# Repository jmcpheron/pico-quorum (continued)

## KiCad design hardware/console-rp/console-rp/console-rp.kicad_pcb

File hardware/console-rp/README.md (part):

# console-rp: the console on an RP2350, with no radio

*Design, 2026-10-29. Written by a script and read back by KiCad 10: the schematic (netlist and ERC)
and the board, routed (DRC). The fab files for JLCPCB are in [console-rp/fab/](console-rp/fab/) and
pass `tools/keypcb jlc console-rp`. Two real panels were checked against J2 ([The panel](#the-panel)).
Five ordered from JLCPCB on 2026-10-29, fully assembled
([the order](../../buildlog/2026-10-29-console-rp-order.md)), and received on 2026-11-04. Four of
them run the console's own image, and one is broken: [The boards and the
firmware](#the-boards-and-the-firmware) has each board and where its notes are.*

![console-rp from above: a warning triangle and EXPERIMENTAL HARDWARE COSIGNER over the 1.14-inch screen at the top left, PicoQuorum console-rp under it, and D0, D1 and D2 in a row below that; the flash, the RP2350, the crystal, the CH343P, and the key chip with an 8-bit key pointing at it, to its right; the USB-C on the right edge, RESET and BOOTSEL at the bottom right, and the bench header's holes along the top](renders/console-rp-top.jpg)

*KiCad's 3D render of the routed board. The panel is drawn as a box. More views are in
[renders/](renders/).*

[console-usb](../console-usb/README.md) took the radio out of use on an ESP32-S3. This board takes
it out of the chip: an **RP2350A** has none. The console talks to the world only through the USB-C
cable it is powered by. A program on the computer fetches the Safe's queue for it and posts its
signatures. The console still rebuilds every hash itself, and the key still signs only that.

```
   Safe's service ── HTTPS ── computer (the relay) ── USB-C ── CH343P ── UART1 ── RP2350A ── I2C0 ── ATECC608C
                              no key, no say in                              screen, D0 D1 D2
                              what gets signed
```

## Why an RP2350

The parts cost about the same as console-usb's: the RP2350A ($1.13 at 100) and its flash ($1.78)
against the S3's $2.52. What it buys is simpler:
- **No radio on the chip at all**, so nothing to keep switched off and no antenna rules.
- **The stock MicroPython image for the Pico 2** (not the W) runs on it, and the console already
  runs on an RP2350 (the Pico 2 W).
- **KiCad 10 ships the RP2350A's symbol and footprint**, and Raspberry Pi publishes the minimal
  circuit around it ("Hardware design with RP2350"). The circuit here is that one.

## Why a serial bridge, not the RP2350's own USB

The RP2350's own USB carries MicroPython's REPL. On this console the cable goes to a computer and
stays there, so any program on that computer could reach the REPL. From there it could make the chip
sign any digest, or call `machine.bootloader()` and write a new image. The bridge closes this with
wiring, as on console-usb:
- The USB-C's D+ and D− go to a **CH343P** (C2846043) and nothing else. It is a standard USB serial
  device (CDC-ACM), so no computer needs a driver.
- Its TXD and RXD go to **UART1** (GPIO21 and GPIO20). MicroPython never puts its REPL there.
- Its **DTR and RTS go nowhere.** The computer can't reset the RP2350 or hold BOOTSEL. DTR is also a
  strap at power-up, so it floats.
- The RP2350's own USB (through Raspberry Pi's 27 Ω) and SWD go to **J3**, a header that isn't
  fitted. Flashing needs J3 and a cable, or SWD and a debug probe: a person with the board in hand.

The generator checks this from KiCad's netlist and stops if it isn't so: the USB-C's data lines,
DTR and RTS, the RP2350's USB and SWD, RUN and BOOTSEL.

## The circuit

| block | parts | notes |
|---|---|---|
| the chip | U1 RP2350A (QFN-60), a 100n at each power pin | USB_OTP_VDD and QSPI_IOVDD share one, as the minimal design |
| its 1.1 V | L1 3.3 µH, C1 and C2 4.7 µF, R1 33 Ω and C3 4.7 µF on VREG_AVDD | the minimal design's. Raspberry Pi says to copy its layout and L1's orientation exactly |
| the clock | Y1 ABM8-272-T3 12 MHz, C15 and C16 15 pF, R2 1 kΩ into XOUT | the crystal and values Raspberry Pi asks for |
| the flash | U6 W25Q128JVSIQ, 16 MB, R3 1 kΩ and SW5 BOOTSEL on QSPI_SS | Basic at JLCPCB, so no fee. The Pico 2 image uses 4 MB of it |
| power | J1 USB-C (5.1k on CC1 and CC2), U2 USBLC6-2SC6, U3 XC6206P332MR | 200 mA is well over what the board draws |
| the link | U4 CH343P | VDD5 and VBUS from the USB-C, V3 on its own 100n, VIO at 3.3 V (WCH's datasheet, 5.2) |
| the key | U5 ATECC608C-SSHDA-T (SOIC-8), R6 and R7 4.7k on I2C0 | SOIC because JLCPCB has 3,972; the UDFN had 27 |
| the screen | J2 ZIF for the 1.14″ 240 × 135 ST7789, Q1, Q2 backlight switch | console-usb's: the same ZIF, panel and pin order |
| buttons | SW1–SW3 D0 D1 D2 in a row under the screen, each to GND | pulled up inside the RP2350, pressed low. Each sits under one of the three footer slots the QT Py console draws |
| reset | SW4 RESET on RUN | |
| bench | J3, 8 holes: GND, 3V3, SWCLK, SWDIO, D−, D+, SDA, SCL | not fitted |

[PINS.md](PINS.md) has the GPIOs. The screen (GPIO 8–13 on SPI1) and the key (GPIO 4 and 5 on I2C0)
are on the Pico's pins, the ones `firmware/board.py` uses by default. The generator checks that, and
checks each GPIO against the RP2350's function table.

**RP2350-E9.** A GPIO with only a weak pull-down can float at about 2 V. Nothing here uses an
internal pull-down. The backlight line's pull-down, R11, is 4.7 kΩ, under the 8.2 kΩ the erratum
asks for.

## Parts at JLCPCB

From JLCPCB's parts search on 2026-10-28. Prices are for one piece and for 100.

| part | LCSC | tier | stock | 1 | 100 |
|---|---|---|---|---|---|
| RP2350A | C42411118 | Extended | 5,521 | $1.30 | $1.13 |
| W25Q128JVSIQ | C97521 | Basic | 66,073 | $2.58 | $1.78 |
| ABM8-272-T3 | C20625731 | Extended | 2,147 | $0.66 | $0.43 |
| AOTA-B201610S3R3-101-T | C42411119 | Extended | **6** | $0.36 | |
| CH343P | C2846043 | Extended | 12,867 | $0.98 | $0.68 |
| ATECC608C-SSHDA-T | C28975195 | Extended | 3,972 | $1.75 | $1.15 |
| XC6206P332MR | C5446 | Basic | 533,724 | $0.15 | |
| USB-C TYPE-C-31-M-12 | C165948 | Extended | 292,653 | $0.19 | |
| USBLC6-2SC6 | C7519 | Extended | 40,704 | $0.18 | |
| ZIF 0.5K-HX-8PWB | C2919492 | Extended | 15,695 | $0.10 | |
| 27 Ω 0402 | C25100 | Extended | 43,619 | $0.001 | |
| AO3401A, SS8050, LED, buttons, the other passives | | Basic | | | |

**About $8.70 of parts a board** at one-piece prices, and about $6.60 at 100. The panel is bought
separately (about $2.50) and clipped into J2 by hand.

**Nine Extended parts, each about $3 a JLCPCB order.** The 27 Ω pair serves only the bench USB on
J3. A Basic 22 Ω would save $3 an order, a little off Raspberry Pi's value.

**L1 is the risk.** JLCPCB has 6 of Raspberry Pi's polarity-marked inductor. Raspberry Pi says its
regulator needs this part, the right way round, in their layout. Before ordering, check the stock,
and plan to pre-order or send our own if it's still short. Its footprint is Raspberry Pi's, from
their minimal design, turned as theirs is.

## The board

72 × 36 mm, two layers, every part on top, ground poured on both sides.
- The panel's glass lies on four 2 mm foam pads at the top left. Under it are only J2, the
  backlight switch and 0402s. The generator checks their heights and keeps them off the pads and
  out of the ribbon's path.
- D0, D1 and D2 sit in a row under the glass, each under the middle of its footer slot.
- The RP2350 is right of the glass. The flash is above-left of it, where its QSPI pins are; the
  regulator is above-right, where VREG is; the crystal is below.
- The CH343P sits between the RP2350 and the USB-C on the right edge.
- The key, RESET, BOOTSEL and the LED are along the bottom; J3 is along the top.
- The silkscreen: a warning triangle and EXPERIMENTAL HARDWARE COSIGNER over the glass, and the
  name under it. On the back: the revision, **picoquorum.dev** and the licence, which names it as
  the Source Location.
  console-s3's 8-bit key (a nod to Adventure) sits beside U5, the key that signs, pointing at it.
  Its dragon is the Easter egg: under the glass, below the ribbon's path, turned to face the key.
  Pixels are 0.4 mm for the key and 0.3 mm for the dragon, so every gap is at least twice JLCPCB's
  0.15 mm.

### The panel

The panel is the common 8-pin 1.14″ ST7789V with a plug-in ribbon. Sellers call it NFP114H-03AF
(printed on the ribbon), NFP114H-03D, N114-2413THBIG09-C08 or Y114-2413THBIG09-C08. YIYANG's
datasheet for the Y114 (rev A, 2020) gives:
- pins 1 LEDA, 2 GND, 3 RESET, 4 RS, 5 SDA, 6 SCL, 7 VDD, 8 CS, at 0.5 mm, the same as J2;
- glass 31.0 × 17.6 × 1.6 mm, with a 23 ± 0.3 mm tail;
- one white LED, its cathode grounded inside, 2.9 to 3.1 V at 20 mA; VDD 2.4 to 3.3 V.

On 2026-10-29 two panels (Walfront's "ST7789V LCD Display Module 1.14 Inch ... Inline Type 2Pcs")
were checked by hand:
- the tail is 23 mm;
- pin 1 is on the side the board expects. With the glass face up and the ribbon leaving its right
  end, pin 1 is nearer the bottom edge, as on the datasheet's drawing. The fold under the glass
  keeps it there, and that is where J2's pad 1 (LEDA) is.

What follows from the datasheet, none of it a change to the board:
- **The ribbon loops, it isn't creased.** The datasheet's tight fold ends 21.0 ± 0.5 mm in from
  the glass's edge, but J2 is about 18.2 mm in. The spare ribbon makes a looser loop, about
  1.5 to 2 mm past the glass's right end by the drawing (not measured). Nothing on the board is
  there; a case needs room for it. console-s3 put its J2 for the tight fold; this board and
  console-usb didn't.
- **The top-right foam pad goes 2.5 mm in from the corner.** At the corner it would sit on U6's
  pins 3 and 4.
- The glass is 0.6 mm wider than the generator's 17.0, which is still the probots listing's figure.
  The extra 0.3 mm each side meets the silkscreen corners and covers nothing new.
- The active area is 1.4 mm off-centre, away from the ribbon. So each button sits 1.4 mm right of
  the middle of its footer slot, well inside the slot's 8 mm.
- R8's 22 Ω gives about 12 to 22 mA, by the datasheet's Vf and a 3.3 V rail within 2%. The high
  end is just past 20 mA. Dim it with PWM, or fit 27 Ω (parts list only) if it runs bright.

Other 1.14″ panels to avoid: the 13-pin N114-2413THBIG01-H13 (another pinout), the solder-type
ribbon, and modules on a small board with a 2.54 mm header (GND on pin 1).

### Round the RP2350: Raspberry Pi's layout

Raspberry Pi says to copy its minimal design's layout, so the board does. `rpi_minimal.py` reads
their KiCad files (MIT, [lib/RPI-MINIMAL-LICENSE.txt](lib/RPI-MINIMAL-LICENSE.txt)) and writes
their footprints for the chip, L1, the crystal and the 0402s into `lib/pqrp.pretty`, and
`rpi_minimal.json`: where each of their parts sits from the chip's centre, their power copper (the
regulator's pours, the rings under the chip, the DVDD and 3V3 tracks and vias), and their crystal's
corner (its lines, ground vias and pour). The generator puts the same
parts at the same places round our U1 and copies their copper, locked. Where ours differs:
- **0.3 mm holes**, not their 0.25: JLCPCB's base price, and our vias'.
- **Their C12 (our C14) moved.** It sat where our flash's lines run; ours is above the USB
  resistors, beside C17.
- **The flash is 1.9 mm nearer the chip,** so its six lines are drawn by hand, as theirs run.
- **Their 27 Ω pair (our R13, R14) is turned round,** as our symbols have the chip on pin 1.
- **Their two ground vias by C1 and C2** were 0.05 mm from those pads' mask openings, where solder
  runs down. The one by C2 moved 0.15 mm out; the one by C1 had no room to move and is left out. C1's
  ground pad reaches the other by a track, and the pour.
- **Our front pour is ground, theirs 3V3,** and it stays out of the regulator's corner, where it
  left scraps between their pours.
- **The back under the chip** is a keep-out for the router, but for their four DVDD tracks, and so
  is the back under the crystal and its capacitors, which on theirs is only ground.

The generator checks the routed board for any other net's copper in their regulator corner or
their crystal's corner, or under the chip or the crystal on the back.

### Routing

Some lines are drawn by hand in `gen_console_rp.py` and locked, because the router left them open
or necked them down: the flash's six, its 3V3 from pin 54, the bench USB to J3, the key's bus out
from pins 7 and 8, SWD and RUN out from pins 24–26, and a few short ties and vias. C17's ground and
the CH343P's exposed pad each get a via the pour can't give them: C17's beside its pad, the
CH343P's in its exposed pad, since its pins shut it in.

`tools/keypcb route console-rp` routed the rest with Freerouting 2.5. The Ground class isn't
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
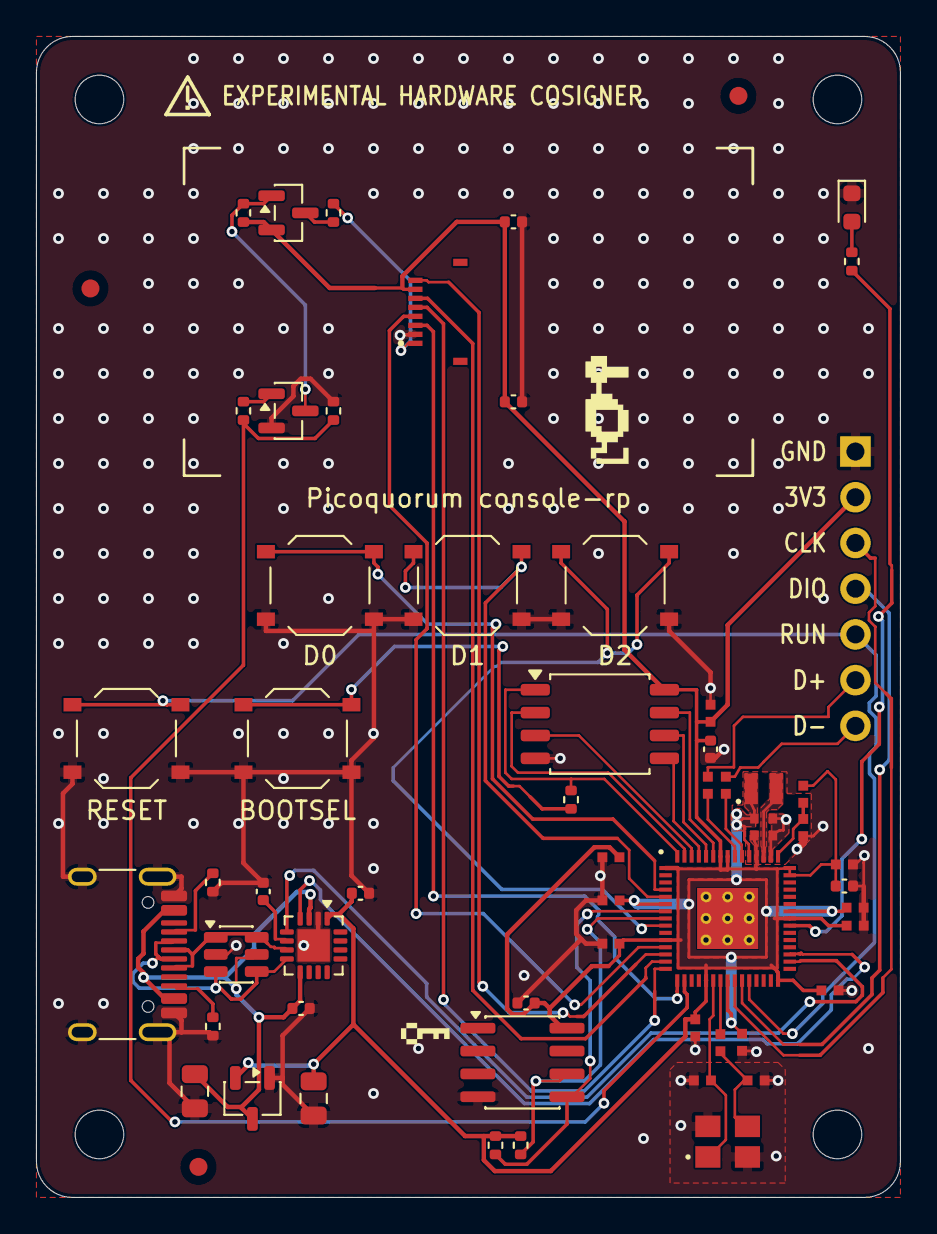
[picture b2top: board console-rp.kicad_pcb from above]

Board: 2 copper layers, 48.0 x 64.5 mm, 67 parts (1 on the bottom side), 47 nets.

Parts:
C1, C2: 4.7u; RPi_C_0402_wide
C3: 4.7u; RPi_C_0402
C4, C5, C6, C7, C8, C10, C11, C12, C13, C14: 100n; RPi_C_0402
C9, C17, C21, C22, C23, C25: 100n; C_0402_1005Metric
C15, C16: 15p; RPi_C_0402
C18, C19: 10u; C_0805_2012Metric
C20, C24: 1u; C_0402_1005Metric
D1: RED; LED_0603_1608Metric
FID1, FID2, FID3: Fiducial; Fiducial_1mm_Mask2mm
H1, H2, H3, H4: M2.5; MountingHole_2.7mm_M2.5
J1: USB-C; USB_C_Receptacle_HRO_TYPE-C-31-M-12
J2: PANEL; FPC_ZIF_8P_P0.5mm_HDGC_0.5K-HX-8PWB
J3: BENCH; PinHeader_1x07_P2.54mm_Vertical
L1: 3.3uH; RPi_L_Abracon_AOTA-B201610
LCD1: 1.14in 240x135; LCD_1.14in_240x135_on_tape
LOGO1: PicoQuorum_Mark
Q1: AO3401A; SOT-23
Q2: S8050; SOT-23
R1: 33R; RPi_R_0402
R2: 1k; RPi_R_0402
R3, R10, R12: 1k; R_0402_1005Metric
R4, R5: 5.1k; R_0402_1005Metric
R6, R7, R11: 4.7k; R_0402_1005Metric
R8: 22R; R_0402_1005Metric
R9: 10k; R_0402_1005Metric
R13, R14: 27R; RPi_R_0402
SW1: D0; SW_Push_1P1T_XKB_TS-1187A
SW2: D1; SW_Push_1P1T_XKB_TS-1187A
SW3: D2; SW_Push_1P1T_XKB_TS-1187A
SW4: RESET; SW_Push_1P1T_XKB_TS-1187A
SW5: BOOTSEL; SW_Push_1P1T_XKB_TS-1187A
U1: RP2350A; RPi_RP2350A_QFN-60_7x7mm_P0.4mm_ThermalVias
U2: USBLC6-2SC6; SOT-23-6
U3: XC6206P332MR; SOT-23-3
U4: CH343P; WCH_QFN-16-1EP_3x3mm_P0.5mm_EP1.8x1.8mm
U5: ATECC608C-SSHDA-T; SOIC-8_3.9x4.9mm_P1.27mm
U6: W25Q128JVSIQ; SOIC-8_5.3x5.3mm_P1.27mm
Y1: 12MHz; RPi_Crystal_SMD_3225-4Pin_3.2x2.5mm

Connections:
+3V3: C1.1, C4.1, C5.1, C6.1, C7.1, C8.1, C9.1, C13.1, C14.1, C17.1, C19.1, C22.1, C23.1, C24.1, C25.1, J2.7, J3.2, Q1.2, R1.1, R6.1, R7.1, R9.1, U1.1, U1.11, U1.20, U1.30, U1.38, U1.44, U1.45, U1.49, U1.53, U1.54, U3.2, U4.1, U5.8, U6.8
/BL_BASE: Q2.1, R10.2
/BL_GATE: Q1.1, Q2.3, R9.2
/BL_SW: Q1.3, R8.1
/BOOT_SW: R3.2, SW5.1
/BTN_D0: SW1.1, U1.4
/BTN_D1: SW2.1, U1.5
/BTN_D2: SW3.1, U1.9
/CC1: J1.A5, R4.1
/CC2: J1.B5, R5.1
/CH_V3: C21.1, U4.6
/DEV_D+: J3.6, R14.2
/DEV_D-: J3.7, R13.2
/DVDD: C2.1, C10.1, C11.1, C12.1, L1.1, U1.6, U1.23, U1.39, U1.50
/LCD_BL: R10.1, R11.1, U1.17
/LCD_CS: J2.8, U1.13
/LCD_DC: J2.4, U1.12
/LCD_LEDA: J2.1, R8.2
/LCD_MOSI: J2.5, U1.15
/LCD_RST: J2.3, U1.16
/LCD_SCK: J2.6, U1.14
/LED: R12.1, U1.37
/LED_A: D1.2, R12.2
/LINK_RX: U1.33, U4.4
/LINK_TX: U1.32, U4.5
/QSPI_SCLK: U1.56, U6.6
/QSPI_SD0: U1.57, U6.5
/QSPI_SD1: U1.59, U6.2
/QSPI_SD2: U1.58, U6.3
/QSPI_SD3: U1.55, U6.7
/QSPI_SS: R3.1, U1.60, U6.1
/RP_DM: R13.1, U1.51
/RP_DP: R14.1, U1.52
/RUN: J3.5, SW4.1, U1.26
/SCL: R7.2, U1.8, U5.6
/SDA: R6.2, U1.7, U5.5
/SWCLK: J3.3, U1.24
/SWDIO: J3.4, U1.25
/USB_D+: J1.A6, J1.B6, U2.1, U2.6, U4.7
/USB_D-: J1.A7, J1.B7, U2.3, U2.4, U4.8
/VREG_AVDD: C3.1, R1.2, U1.46
/VREG_LX: L1.2, U1.48
/XIN: C15.1, U1.21, Y1.1
/XOUT: R2.1, U1.22
/XTAL_OUT: C16.1, R2.2, Y1.3
GND: C1.2, C2.2, C3.2, C4.2, C5.2, C6.2, C7.2, C8.2, C9.2, C10.2, C11.2, C12.2, C13.2, C14.2, C15.2, C16.2, C17.2, C18.2, C19.2, C20.2, C21.2, C22.2, C23.2, C24.2, C25.2, D1.1, J1.A1, J1.A12, J1.B1, J1.B12, J1.SH, J2.2, J3.1, Q2.2, R4.2, R5.2, R11.2, SW1.2, SW2.2, SW3.2, SW4.2, SW5.2, U1.47, U1.61, U2.2, U3.1, U4.2, U4.17, U5.4, U6.4, Y1.2, Y1.4
VBUS: C18.1, C20.1, J1.A4, J1.A9, J1.B4, J1.B9, U2.5, U3.3, U4.3, U4.9

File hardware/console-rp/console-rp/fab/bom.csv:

Comment,Designator,Footprint,LCSC Part #
4.7u,"C1,C2",RPi_C_0402_wide,C23733
15p,"C15,C16",RPi_C_0402,C1548
10u,"C18,C19",C_0805_2012Metric,C15850
1u,"C20,C24",C_0402_1005Metric,C52923
4.7u,C3,RPi_C_0402,C23733
100n,"C4,C5,C6,C7,C8,C10,C11,C12,C13,C14",RPi_C_0402,C1525
100n,"C9,C17,C21,C22,C23,C25",C_0402_1005Metric,C1525
RED,D1,LED_0603_1608Metric,C2286
USB-C,J1,USB_C_Receptacle_HRO_TYPE-C-31-M-12,C165948
PANEL,J2,FPC_ZIF_8P_P0.5mm_HDGC_0.5K-HX-8PWB,C2919492
3.3uH,L1,RPi_L_Abracon_AOTA-B201610,C42411119
AO3401A,Q1,SOT-23,C15127
S8050,Q2,SOT-23,C2150
33R,R1,RPi_R_0402,C25105
27R,"R13,R14",RPi_R_0402,C25100
1k,R2,RPi_R_0402,C11702
1k,"R3,R10,R12",R_0402_1005Metric,C11702
5.1k,"R4,R5",R_0402_1005Metric,C25905
4.7k,"R6,R7,R11",R_0402_1005Metric,C25900
22R,R8,R_0402_1005Metric,C25092
10k,R9,R_0402_1005Metric,C25744
D0,SW1,SW_Push_1P1T_XKB_TS-1187A,C318884
D1,SW2,SW_Push_1P1T_XKB_TS-1187A,C318884
D2,SW3,SW_Push_1P1T_XKB_TS-1187A,C318884
RESET,SW4,SW_Push_1P1T_XKB_TS-1187A,C318884
BOOTSEL,SW5,SW_Push_1P1T_XKB_TS-1187A,C318884
RP2350A,U1,RPi_RP2350A_QFN-60_7x7mm_P0.4mm_ThermalVias,C42411118
USBLC6-2SC6,U2,SOT-23-6,C7519
XC6206P332MR,U3,SOT-23-3,C5446
CH343P,U4,WCH_QFN-16-1EP_3x3mm_P0.5mm_EP1.8x1.8mm,C2846043
ATECC608C-SSHDA-T,U5,SOIC-8_3.9x4.9mm_P1.27mm,C28975195
W25Q128JVSIQ,U6,SOIC-8_5.3x5.3mm_P1.27mm,C97521
12MHz,Y1,RPi_Crystal_SMD_3225-4Pin_3.2x2.5mm,C20625731

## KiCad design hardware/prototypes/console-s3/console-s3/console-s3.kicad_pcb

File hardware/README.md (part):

# hardware

Console and key electronics. The goals are in [`../docs/KICKOFF.md`](../docs/KICKOFF.md).

The work is on **Mono**. Everything else here is the board it comes from, the keys, the dev console
that runs the firmware today, or kept for the record.

| | what it is | where it stands |
|---|---|---|
| **[Mono](mono/README.md)** | the reference console: an RP2350A with no radio, the ATECC608C on the board, a 1.14″ screen and three buttons on a 40 × 89.5 mm bar | designed and routed, 2026-11-06. Its fab files pass `tools/keypcb jlc mono`. Not ordered, nothing built |
| [Tally](tally/README.md) | Mono's console drawn again from scratch: the same bar, pins and screen; the core fed by a plain 1.1 V regulator, so no inductor; the chip's own USB not brought out | designed, routed and reviewed, 2026-11-13, with KiCad 7: netlist and DRC clean. `tools/keypcb check` and `jlc` not run on it. Not ordered, nothing built |
| **[Mono's case](../cad/consoles/README.md#mono)** | a printed shell and back panel, and [the industrial variant](../cad/consoles/README.md#mono-industrial) with cut corners and grooves | first drafts, not printed |
| [console-rp](console-rp/README.md) | the board Mono comes from: the same RP2350A, link, key, screen and pins, on 72 × 36 mm | 5 boards received 2026-11-04. The first is up on a bench script; the console's firmware for it isn't written |
| [key-c and the other keys](key-pcb/README.md) | the key as a part you plug in: an ATECC608C behind a USB-C receptacle | key-c P2 built and working; P3 drawn |
| [the dev console](DEV-CONSOLE.md) | a Pico 2 W, a Waveshare screen and an ATECC608 breakout, no soldering | runs the console image today |
| [prototypes/](prototypes/README.md) | the two ESP32-S3 boards with their own Wi-Fi: console-s3 and PicoquorumKey | both made; the first board of each runs |
| [archive/](archive/README.md) | earlier boards and builds, no longer worked on | as they were on 2026-11-11 |

## Mono

*KiCad's 3D render of the routed board. The panel is drawn as a box.*

Mono is a working name. It is the design the others are measured against:
- **No radio.** The USB-C reaches a serial chip and nothing else. A computer passes on Safe's queue;
  the console rebuilds every hash itself, and the key signs only that.
- **The key on the board,** an ATECC608C, and a site for a second key on a bus and a supply of its own.
- **Every part JLCPCB fits is on the front,** for Economic assembly; the screen goes on by hand. Nine
  pads on the back are for a pogo jig.
- **console-rp's pins,** so console-rp's image will run on it unchanged.

**Its case** is in [`cad/consoles/`](../cad/consoles/README.md), drawn by scripts:

| | script | build | outputs |
|---|---|---|---|
| Mono's case | [`mono.py`](../cad/consoles/mono.py) | `tools/case build mono` | [`out/mono/`](../cad/consoles/out/mono/) |
| the industrial variant | [`mono_ind.py`](../cad/consoles/mono_ind.py) | `tools/case build mono-industrial` | [`out/mono_ind/`](../cad/consoles/out/mono_ind/) |

[`cad/mono/`](../cad/mono/README.md) is the board itself as a print, to hold. The enclosure's open
questions (a guard over Sign, printed or aluminum, the name on the face) are in the kickoff's
[open decisions](../docs/KICKOFF.md#open-decisions).

## What is in this folder

- [`mono/`](mono/README.md): Mono's board. Its generator, the KiCad project, fab files, renders and
  [pins](mono/PINS.md)
- [`tally/`](tally/README.md): a second, independent design of Mono's console. Its generator, the KiCad
  project, fab files and [pins](tally/PINS.md)
- [`console-rp/`](console-rp/README.md): the first RP2350 console. Its
  [bring-up](console-rp/bench/BRINGUP.md), [the plan](console-rp/PLAN-2026-11-04.md) written the
  night it came up, and [a plan for a square rev B](console-rp/REV-B-PLAN-2026-11-05.md)
- [`key-pcb/`](key-pcb/README.md): the keys' boards, [key-c](key-pcb/key-c-usbc/README.md) among
  them, and how to order them ([ORDERING.md](key-pcb/ORDERING.md))
- [`DEV-CONSOLE.md`](DEV-CONSOLE.md), [`bom/`](bom/README.md) and [`wiring/`](wiring/): the dev
  console and the other builds from bought boards that the firmware has a profile for.
  [Build 1](wiring/BUILD1.md), [on a breadboard](wiring/BREADBOARD.md),
  [on an ESP32](wiring/ESP32.md), [on a Feather](wiring/FEATHER-S3.md), and the
  [perfboard wiring](wiring/SOLDERING.md) from picowallet (`tools/wiring`)
- [`prototypes/`](prototypes/README.md): console-s3 and PicoquorumKey, and the plan they were
  ordered from
- [`archive/`](archive/README.md): console-a (two of them), console-pocket, console-usb, the
  Feather's wings, and four builds that were written up and not wired

`tools/keypcb` checks, routes and writes fab files for the boards, wherever they are
(`tools/keypcb check mono`). `tools/case` rebuilds the printed cases.

## Every configuration

Two kinds: **builds**, put together from bought boards, and **boards** we design. The firmware
column is the console image's `BOARD` profile (`firmware/board.py`); a build's own test and demo
screens are bench scripts, never part of the image
([archive/builds/](archive/builds/README.md#firmware)).

| name | kind | the key | firmware | where it stands |
|---|---|---|---|---|
| **[Mono](mono/README.md)** | board | ATECC608C (SOIC-8) on the board; a second key's site, not fitted | console-rp's profile, not written | routed, not ordered |
| [console-rp](console-rp/README.md) | board | ATECC608C (SOIC-8) on the board | a `console-rp` profile, not written | 5 received 2026-11-04 ([order](../buildlog/2026-10-29-console-rp-order.md)); the first is up on a bench script |
| [key-c and the other keys](key-pcb/README.md) | board | — | — | key-c P2 built and working; P3 drawn |
| [dev console](DEV-CONSOLE.md) | build | ATECC608 breakout, STEMMA QT | `waveshare` | the no-solder build |
| [Build 1](wiring/BUILD1.md), [on a breadboard](wiring/BREADBOARD.md) | build | ATECC608 on TRRS jacks | `build1` | — |
| [ESP32 DevKit](wiring/ESP32.md) | build | ATECC608 breakout | `esp32` | the console ran on a WROVER |
| [Feather + adapters](wiring/FEATHER-S3.md) | build | key-c, STEMMA QT to USB-C adapters | `feather-s3`; bench in [wiring/feather-s3/](wiring/feather-s3/) | runs; chip 3 through the ceremony, 2026-10-22 |

Early prototypes ([prototypes/](prototypes/README.md)):

| name | kind | the key | firmware | where it stands |
|---|---|---|---|---|
| [console-s3](prototypes/console-s3/DESIGN.md) | board | ATECC608C on the board | `feather-s3` | 5 boards came 2026-11-02; board 1 runs ([its first day](../buildlog/2026-11-02-console-s3-first-board.md)) |
| [picoquorum-key](prototypes/picoquorum-key/README.md) | board | UDFN ATECC608C on the board; rev B adds a key port for key-c | `picoquorum-key`, picked by its key bus's pull-ups; the port needs a later image | boards made, rev B; the first reported working, 2026-11-03 ([build log](../buildlog/BUILDLOG.md)) |

Archived ([archive/](archive/README.md)):

| name | kind | the key | firmware | where it stood |
|---|---|---|---|---|
| [console-a (console-pcb)](archive/console-pcb/README.md) | board | key-c, USB-C | `build1` | designed |
| [console-a](archive/console-a/README.md) | board | pads | `waveshare` | designed, not ordered |
| [console-pocket](archive/console-pocket/README.md) | board | pads | `waveshare` | not checked in KiCad, not ordered |
| [console-usb](archive/console-usb/README.md) | board | ATECC608C on the board | `feather-s3`, plus firmware not written | not routed |
| [feather-wing a, b](archive/feather-wing/README.md) | board | key-c, USB-C | `feather-s3` | not ordered |
| [Feather pigtail](archive/builds/feather-pigtail/README.md) | build | key-c, a USB-C cable soldered to the pins | `feather-s3`; bench `swap.py`; a case | written up, not wired |
| [Feather knob](archive/builds/feather-knob/README.md) | build | key-c, a USB-C adapter on the header pins | `feather-knob` (knob and Boot); bench `dial.py` | written up, not wired |
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
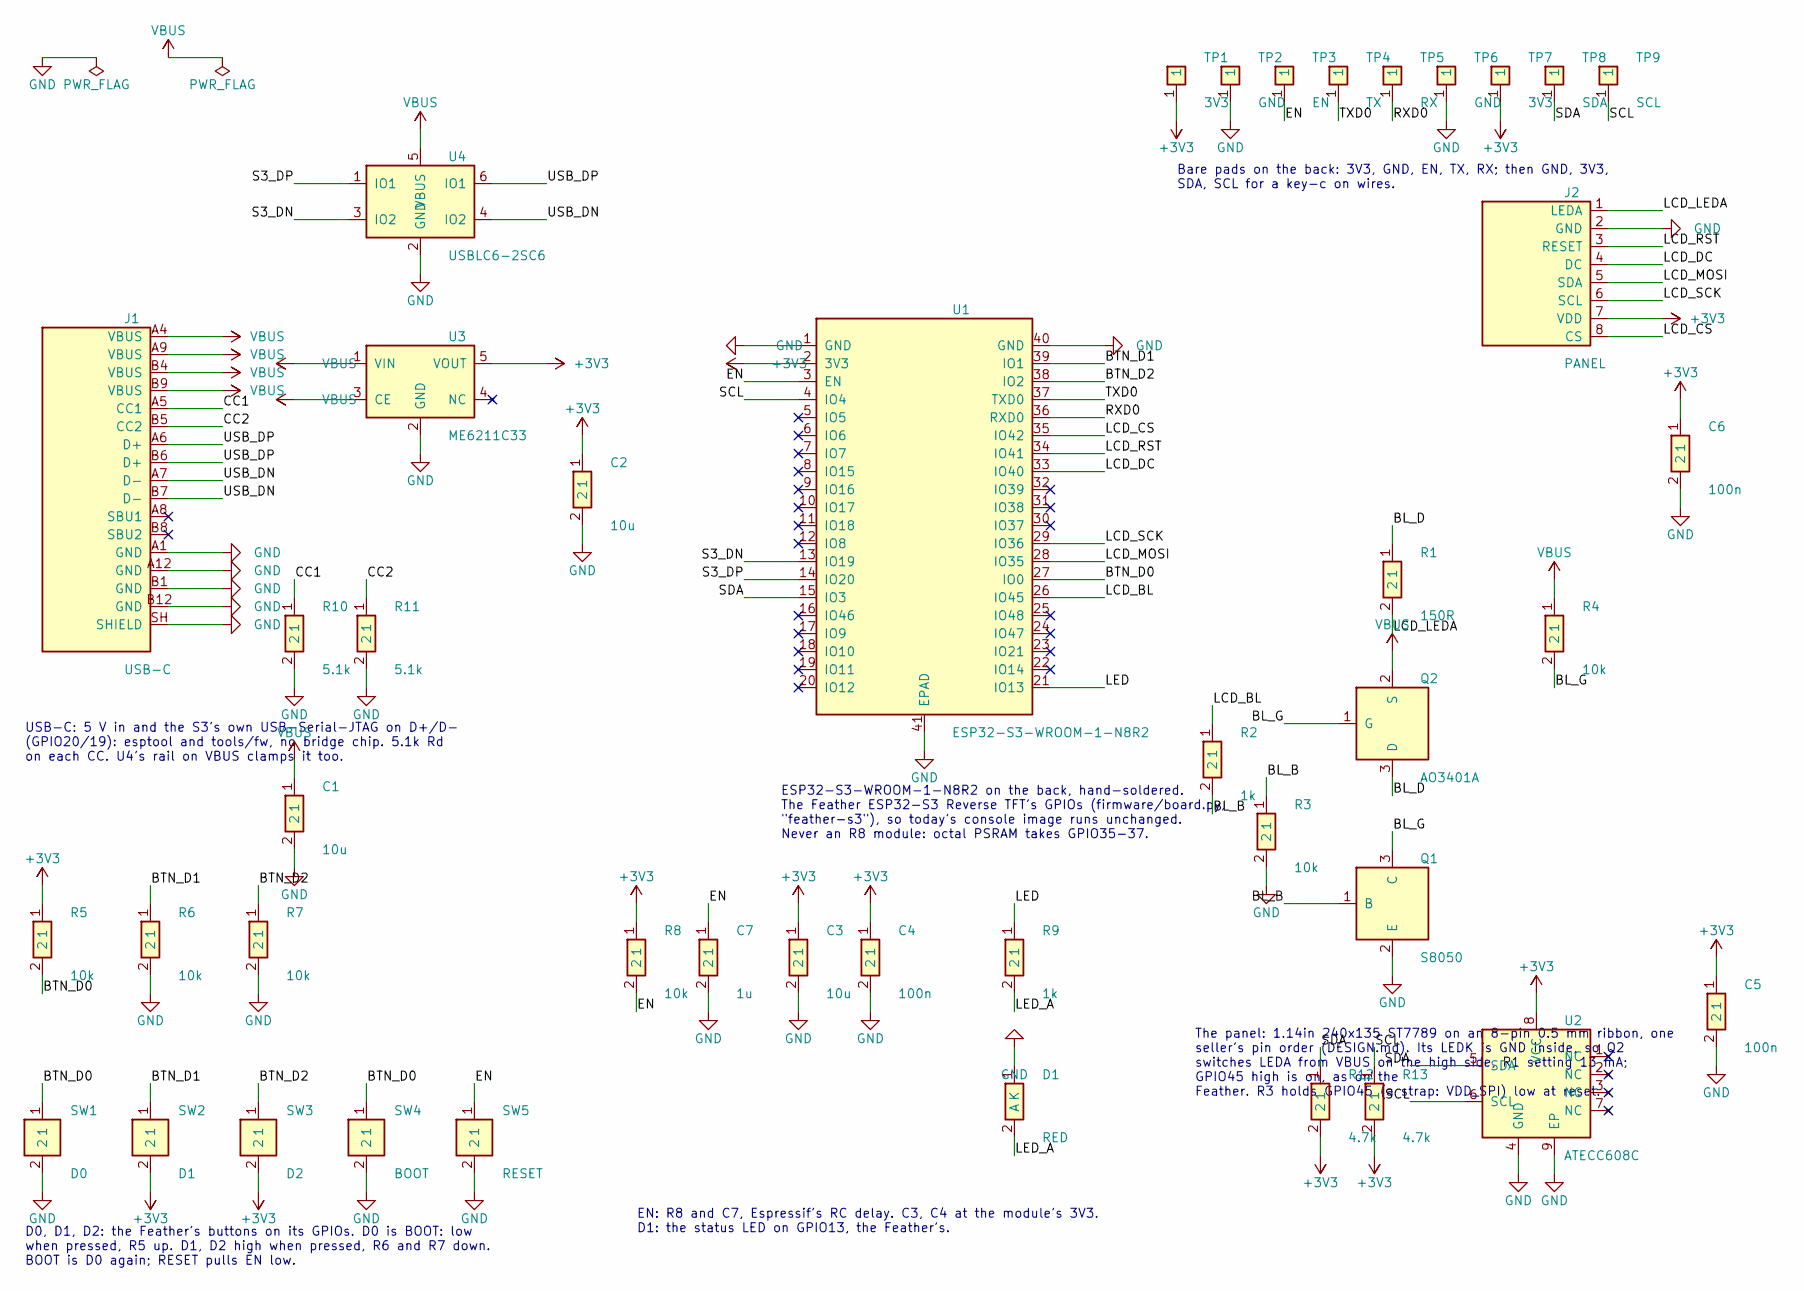
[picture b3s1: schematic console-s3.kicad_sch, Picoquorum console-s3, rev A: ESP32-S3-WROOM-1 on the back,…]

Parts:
C1, C2, C3: 10u; C_0603; LCSC C19702
C4, C5, C6: 100n; C_0603; LCSC C14663
C7: 1u; C_0603; LCSC C15849
D1: RED; LED_0603; LCSC C2286
J1: USB-C; USB_C_Receptacle_HCTL_HC-TYPE-C-16P-01A; MPN HC-TYPE-C-16P-01A; LCSC C2894897
J2: PANEL; FPC_ZIF_8P_P0.5mm_HDGC_0.5K-HX-8PWB; MPN 0.5K-HX-8PWB; LCSC C2919492
Q1: S8050; SOT-23; MPN SS8050; LCSC C2150
Q2: AO3401A; SOT-23; MPN AO3401A; LCSC C15127
R1: 150R; R_0603; LCSC C22808
R2, R9: 1k; R_0603; LCSC C21190
R3, R4, R5, R6, R7, R8: 10k; R_0603; LCSC C25804
R10, R11: 5.1k; R_0603; LCSC C23186
R12, R13: 4.7k; R_0603; LCSC C23162
SW1: D0; SW_TS-1187A; MPN TS-1187A-B-A-B; LCSC C318884
SW2: D1; SW_TS-1187A; MPN TS-1187A-B-A-B; LCSC C318884
SW3: D2; SW_TS-1187A; MPN TS-1187A-B-A-B; LCSC C318884
SW4: BOOT; SW_TS-1187A; MPN TS-1187A-B-A-B; LCSC C318884
SW5: RESET; SW_TS-1187A; MPN TS-1187A-B-A-B; LCSC C318884
TP1, TP7: 3V3; TestPad_1.5mm_Back
TP2, TP6: GND; TestPad_1.5mm_Back
TP3: EN; TestPad_1.5mm_Back
TP4: TX; TestPad_1.5mm_Back
TP5: RX; TestPad_1.5mm_Back
TP8: SDA; TestPad_1.5mm_Back
TP9: SCL; TestPad_1.5mm_Back
U1: ESP32-S3-WROOM-1-N8R2; ESP32-S3-WROOM-1; MPN ESP32-S3-WROOM-1-N8R2
U2: ATECC608C; DFN-8-1EP_3x2mm_P0.5mm; MPN ATECC608C-MAHDA-S; LCSC C23291019
U3: ME6211C33; SOT-23-5; MPN ME6211C33M5G-N; LCSC C82942
U4: USBLC6-2SC6; SOT-23-6; MPN USBLC6-2SC6; LCSC C7519

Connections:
+3V3: C2.1, C3.1, C4.1, C5.1, C6.1, J2.7 (VDD), R5.1, R8.1, R12.2, R13.2, SW2.2, SW3.2, TP1.1, TP7.1, U1.2 (3V3), U2.8 (VCC), U3.5 (VOUT)
/BL_B: Q1.1 (B), R2.2, R3.1
/BL_D: Q2.3 (D), R1.1
/BL_G: Q1.3 (C), Q2.1 (G), R4.2
/BTN_D0: R5.2, SW1.1, SW4.1, U1.27 (IO0)
/BTN_D1: R6.1, SW2.1, U1.39 (IO1)
/BTN_D2: R7.1, SW3.1, U1.38 (IO2)
/CC1: J1.A5 (CC1), R10.1
/CC2: J1.B5 (CC2), R11.1
/EN: C7.1, R8.2, SW5.1, TP3.1, U1.3 (EN)
/LCD_BL: R2.1, U1.26 (IO45)
/LCD_CS: J2.8 (CS), U1.35 (IO42)
/LCD_DC: J2.4 (DC), U1.33 (IO40)
/LCD_LEDA: J2.1 (LEDA), R1.2
/LCD_MOSI: J2.5 (SDA), U1.28 (IO35)
/LCD_RST: J2.3 (RESET), U1.34 (IO41)
/LCD_SCK: J2.6 (SCL), U1.29 (IO36)
/LED: R9.1, U1.21 (IO13)
/LED_A: D1.2 (A), R9.2
/RXD0: TP5.1, U1.36 (RXD0)
/S3_DN: U1.13 (IO19), U4.3 (IO2)
/S3_DP: U1.14 (IO20), U4.1 (IO1)
/SCL: R13.1, TP9.1, U1.4 (IO4), U2.6 (SCL)
/SDA: R12.1, TP8.1, U1.15 (IO3), U2.5 (SDA)
/TXD0: TP4.1, U1.37 (TXD0)
/USB_DN: J1.A7 (D-), J1.B7 (D-), U4.4 (IO2)
/USB_DP: J1.A6 (D+), J1.B6 (D+), U4.6 (IO1)
GND: C1.2, C2.2, C3.2, C4.2, C5.2, C6.2, C7.2, D1.1 (K), J1.A1 (GND), J1.A12 (GND), J1.B1 (GND), J1.B12 (GND), J1.SH (SHIELD), J2.2 (GND), Q1.2 (E), R3.2, R6.2, R7.2, R10.2, R11.2, SW1.2, SW4.2, SW5.2, TP2.1, TP6.1, U1.1 (GND), U1.40 (GND), U1.41 (EPAD), U2.4 (GND), U2.9 (EP), U3.2 (GND), U4.2 (GND)
VBUS: C1.1, J1.A4 (VBUS), J1.A9 (VBUS), J1.B4 (VBUS), J1.B9 (VBUS), Q2.2 (S), R4.1, U3.1 (VIN), U3.3 (CE), U4.5 (VBUS)

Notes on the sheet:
ESP32-S3-WROOM-1-N8R2 on the back, hand-soldered. The Feather ESP32-S3 Reverse TFT's GPIOs (firmware/board.py, "feather-s3"), so today's console image runs unchanged. Never an R8 module: octal PSRAM takes GPIO35-37.
USB-C: 5 V in and the S3's own USB-Serial-JTAG on D+/D- (GPIO20/19): esptool and tools/fw, no bridge chip. 5.1k Rd on each CC. U4's rail on VBUS clamps it too.
The panel: 1.14in 240x135 ST7789 on an 8-pin 0.5 mm ribbon, one seller's pin order (DESIGN.md). Its LEDK is GND inside, so Q2 switches LEDA from VBUS on the high side, R1 setting 13 mA; GPIO45 high is on, as on the Feather. R3 holds GPIO45 (a strap: VDD_SPI) low at reset.
D0, D1, D2: the Feather's buttons on its GPIOs. D0 is BOOT: low when pressed, R5 up. D1, D2 high when pressed, R6 and R7 down. BOOT is D0 again; RESET pulls EN low.
EN: R8 and C7, Espressif's RC delay. C3, C4 at the module's 3V3. D1: the status LED on GPIO13, the Feather's.
Bare pads on the back: 3V3, GND, EN, TX, RX; then GND, 3V3, SDA, SCL for a key-c on wires.

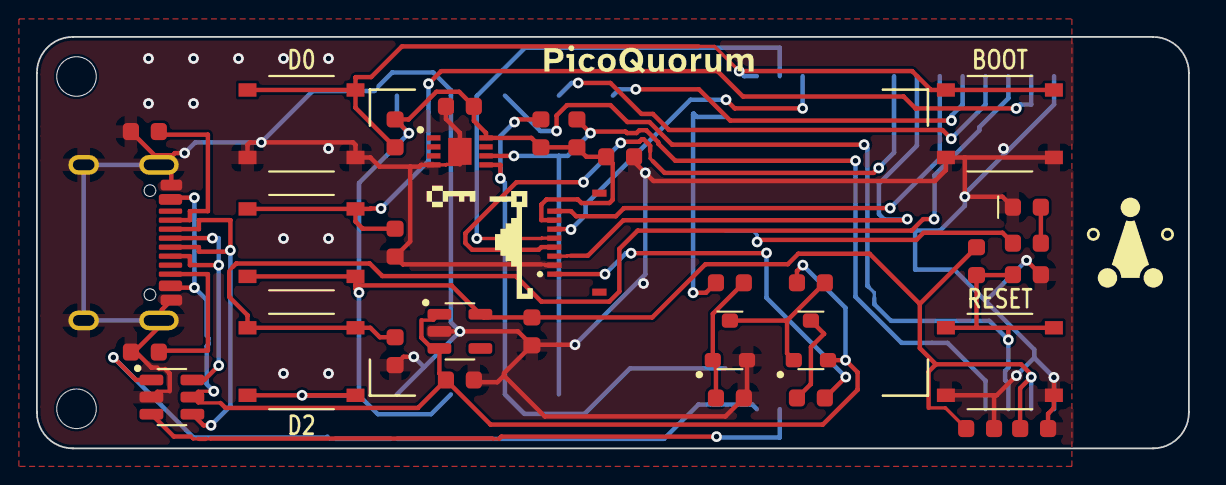
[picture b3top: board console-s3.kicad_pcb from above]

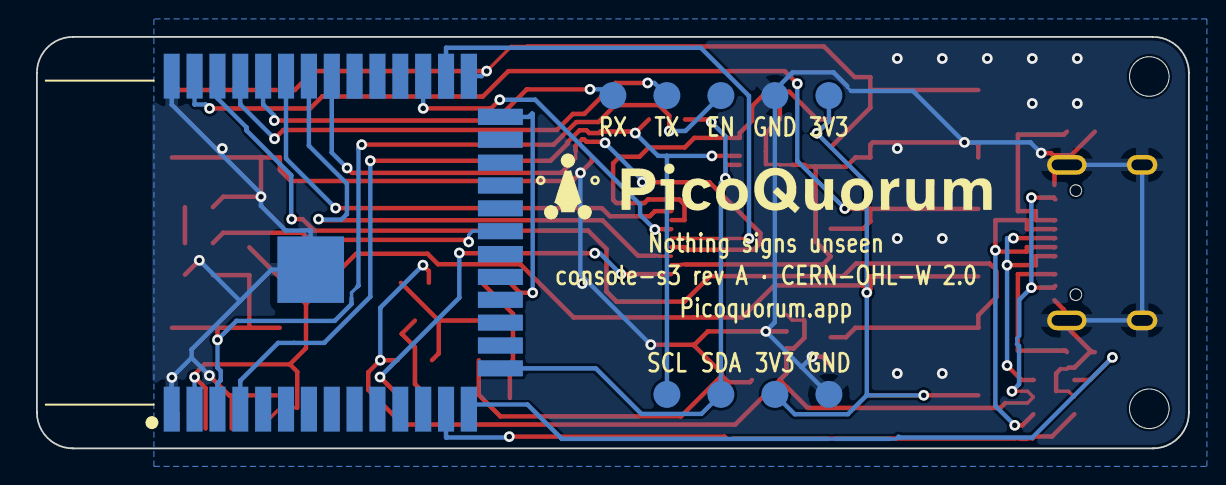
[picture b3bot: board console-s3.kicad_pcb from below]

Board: 2 copper layers, 64.0 x 22.9 mm, 45 parts (10 on the bottom side), 29 nets.

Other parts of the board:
H1, H2: M2; MountingHole_2.2mm

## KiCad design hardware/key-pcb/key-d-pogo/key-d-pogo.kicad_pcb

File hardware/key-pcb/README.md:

# Key PCB

*Rev A, designed 2026-10-02, not yet ordered.*

On rev A the PCB is the plug. The key is a small board with gold fingers on one edge, like a
YubiKey. Those fingers slide into a card-edge socket on the console, so there are no audio plugs,
no wires, and nothing to solder to plug lugs. The secure element sits on the same board.

| key-b (UDFN, assembled) | key-a (SOIC, hand-soldered) | back |
|---|---|---|
|  |  |  |

The renders come from `tools/keypcb render`. They show the pads, fingers and silkscreen but no
part bodies, because KiCad's 3D models aren't installed where they were made.

## The fingers

Fingers of different lengths sequence the contacts in copper, the way PCIe's presence pins do. A
finger that starts closer to the edge touches its contact sooner.

| position | signal | finger | console | why |
|---|---|---|---|---|
| 1 | GND | long: 0.5 mm from the edge | GND | mates first, breaks last |
| 2 | SDA | mid: 1.25 mm | GP4 | |
| 3 | SCL | mid | GP5 | |
| 4 | VCC | mid | GP6, switched key power | |
| 5 | KEY ID | mid | GP27 / ADC1 | R1 to GND, not fitted on rev A |
| 6 | *keying slot* | none | | the connector's key insert goes here |
| 7 | RST | mid | GP26 | Trust M only; open on an ATECC key |
| 8 | DETECT | short: 2.0 mm | GP7, pull-up | tied to GND on the key; mates last, breaks first |

These are **Build 1's GPIOs, so the firmware doesn't change.** The power sequence in
[BUILD1.md](../wiring/BUILD1.md#how-the-key-is-detected-and-powered) still applies:
- DETECT reads low only once the key is at full depth.
- The console then switches VCC on.
- DETECT breaks first on the way out, so VCC is already off before anything else lets go.

On the board:
- **Fingers are on the top side only.** A key put in upside down meets the console's unused contact
  row. DETECT never goes low, so it is never powered. The keying slot stops it going in that way at
  all, but even without the slot an upside-down key would be inert, not damaged.
- **Every finger ends 8.5 mm from the edge.** EDAC's drawing puts a seated card's contact point
  about 4.3 mm in, so it lands well inside every finger. Sullins doesn't publish its contact point.
  The short finger starts at 2.0 mm so a shallower contact still lands on it.
- **The fingers are 1.40 mm wide at 2.54 mm pitch.** The blade is 22.35 mm wide (an 8-position
  0.062″ card is 0.888″ +0/−0.015″), with 0.8 mm chamfers on the leading corners.
- **No I2C pull-ups on the key.** They stay on the console, to switched VCC, as in Build 1.

## The circuit

| ref | part | why |
|---|---|---|
| U1 | ATECC608C: SOIC-8 on key-a, UDFN-8 2×3 mm on key-b | the key's P-256 signing key |
| U2 | USBLC6-2SC6 (SOT-23-6) | ESD on SDA, SCL and VCC: people handle and hot-plug the key |
| C1 | 100 nF: 0805 on key-a, 0402 on key-b | decoupling, next to U1 pin 8 |
| R1 | not fitted | KEY ID code to GND, for later |
| J1 | the fingers | not a part: copper on the board edge |

Layout notes:
- **U2 sits between the fingers and the chip.** Each line runs straight through it, pins 1 to 6 and
  3 to 4, as ST's layout does.
- **U2's rail pin is VCC**, so with the key unpowered a voltage on SDA or SCL would leak into VCC
  through it. The console already avoids this: with the key out, SDA and SCL are plain inputs with
  no pull-ups.
- **Ground.** Both layers are a ground pour, kept off the finger zone by a rule area. The UDFN's
  centre pad goes to GND, as Microchip recommends.

**P-256 is fine.** The ATECC608 family signs P-256 only, never secp256k1, and Picoquorum never
used k1:
- Each chip key owns the Safe through Safe's passkey signer
  ([webauthn.py](../../firmware/webauthn.py)).
- On Base it is verified by the P-256 precompile ([contracts](../../contracts/README.md)).

The ATECC608C's I2C address as shipped is 0x60, one of the addresses `signer.detect()` already
tries.

## Files

| path | what |
|---|---|
| `key-a-soic/`, `key-b-udfn/` | the two KiCad 9 projects: open the `.kicad_pro` |
| `*/fab/` | what you upload: `*-gerbers.zip` (Gerbers + drill), `bom.csv` and `cpl.csv` in JLCPCB's format, and the renders |
| `lib/` | the project's symbols (`picoquorum.kicad_sym`) and the blade footprint (`picoquorum.pretty`) |
| `gen.py` | wrote all of the above. Once you edit a board in KiCad, the KiCad files win: don't run it again |
| [`ORDERING.md`](ORDERING.md) | how to read the design in KiCad, check it, export it and order it |
| [`LEARN.md`](LEARN.md) | a guided tour of rev A for PCB beginners, with the numbers behind each part |
| `keycalc.py` | `tools/keypcb calc`: finger timing, I2C rise time, GPIO power and SPICE runs (plots in `out/`, ignored) |
| [`key-c-usbc/README.md`](key-c-usbc/README.md) | **ordered 2026-10-02**: key-c P2's status page, newest first, with renders |
| [`PROPOSALS.md`](PROPOSALS.md) | proposals C and D: the same circuit on a USB-C receptacle (`key-c-usbc/`) or pogo pads with magnets (`key-d-pogo/`), written by `gen_cd.py` |

`tools/keypcb check` runs ERC, then DRC with schematic parity, on both boards. `fab` rewrites
`fab/` and `render` redraws the images. Both boards check clean: 0 ERC errors, 0 DRC
violations, 0 unconnected, parity clean.

## The console side

Rev A uses a stock card-edge socket for 0.062″ cards at 0.100″ pitch, with 8 positions per row.
Wire only the top row to the Pico, with the GPIOs above.

| part | Digi-Key | notes |
|---|---|---|
| Sullins EBC08DRXN, 8/16 positions, dual readout, solder tails | check stock; the 5/10 size is S9641-ND | in stock in the family; PBT body, so hand- or wave-solder it, never reflow; 500 cycles |
| Sullins PLA-K1 key | PLA-K1-ND | Sullins' catalog says "between contacts", Digi-Key says "on contact": see below |
| EDAC 395 series (alternative) | 151-1420-ND (10-contact) | the drawing these numbers come from; low stock |

## Trust M later

A Trust M key (key-c) uses the same blade and finger map:
- RST on position 7.
- I2C address 0x30, which `signer.detect()` already polls.
- The chip comes in a 3×3 mm USON-10. KiCad's `Microchip_USON-10-1EP_3x3mm_P0.5mm_EP1.8x2.5mm` is a
  starting point, but check it against Infineon's land pattern first.

KEY ID (R1 on position 5) can then tell the console which chip a key carries before it says a
word on I2C.

## Open

- [ ] Order rev A and test-fit a bare board in the socket before trusting the 22.35 mm width, the
      finger depth and the key slot ([ORDERING.md](ORDERING.md))
- [ ] Which way the Sullins PLA-K1 sits. Position 6 has a 2.03 mm slot for an in-contact key, as
      EDAC draws it. A between-contacts key would need a slot next to a finger instead, or no key
      at all, since an upside-down key is inert anyway
- [ ] Sullins' contact point. If it sits shallower than 2 mm, move the finger starts closer to the
      edge
- [ ] ENIG is soft gold, good for a prototype. For keys that see daily use, rev B can move to
      JLCPCB's bevelled gold fingers, which need a board or panel of at least 50 × 50 mm
- [ ] Pull-ups: BUILD1's 10k is marginal for the ATECC608C's 300 ns rise time above 100 kHz.
      4.7k is safer
- [ ] KEY ID resistor codes per key type ([open decisions](../../docs/STATUS.md#open-decisions))
- [x] A socket breakout PCB for the console (rev B): the console boards bring the key out
      themselves, [console-pcb](../archive/console-pcb/README.md) as a USB-C plug, [console-a](../archive/console-a/README.md)
      and [console-pocket](../archive/console-pocket/README.md) as pads
- [ ] The key's shell, if any

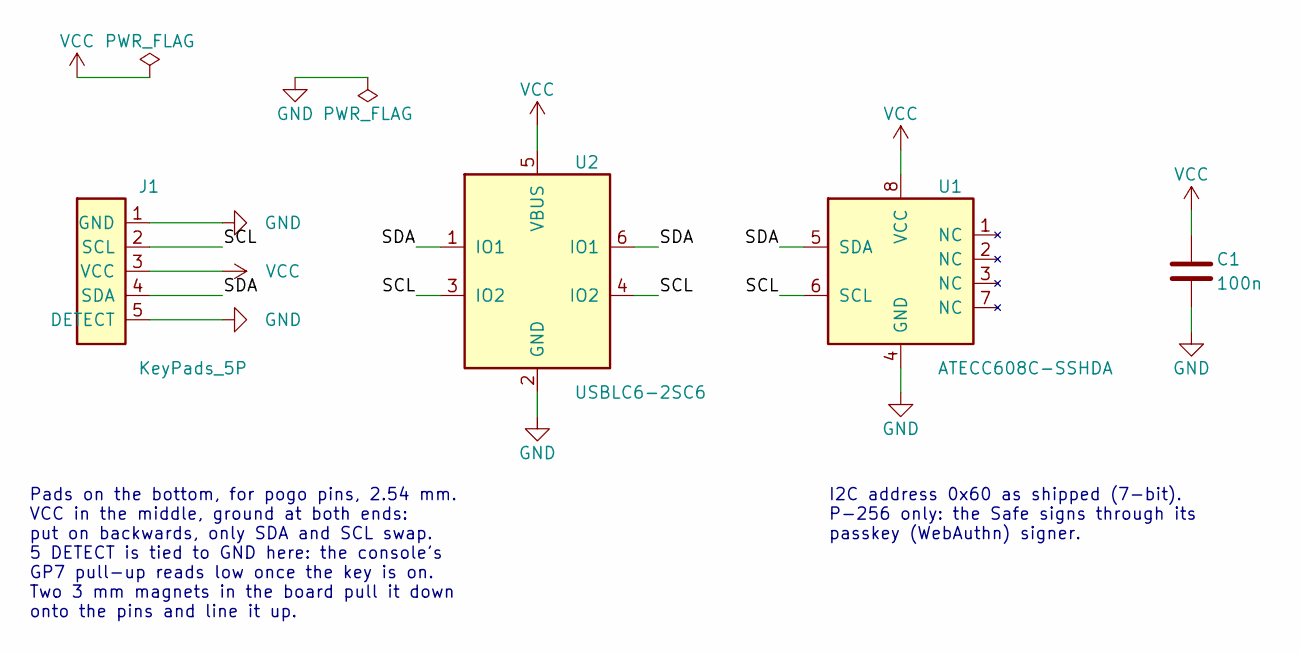
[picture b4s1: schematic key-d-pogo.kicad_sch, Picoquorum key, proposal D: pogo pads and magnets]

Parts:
C1: 100n; C_0805_2012Metric; LCSC C49678
J1: KeyPads_5P; KeyPads_5P_P2.54mm
U1: ATECC608C-SSHDA; SOIC-8_3.9x4.9mm_P1.27mm; MPN ATECC608C-SSHDA-B; LCSC C28975195
U2: USBLC6-2SC6; SOT-23-6; MPN USBLC6-2SC6; LCSC C7519

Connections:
/SCL: J1.2 (SCL), U1.6 (SCL), U2.3 (IO2), U2.4 (IO2)
/SDA: J1.4 (SDA), U1.5 (SDA), U2.1 (IO1), U2.6 (IO1)
GND: C1.2, J1.1 (GND), J1.5 (DETECT), U1.4 (GND), U2.2 (GND)
VCC: C1.1, J1.3 (VCC), U1.8 (VCC), U2.5 (VBUS)

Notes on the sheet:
I2C address 0x60 as shipped (7-bit). P-256 only: the Safe signs through its passkey (WebAuthn) signer.
Pads on the bottom, for pogo pins, 2.54 mm. VCC in the middle, ground at both ends: put on backwards, only SDA and SCL swap. 5 DETECT is tied to GND here: the console's GP7 pull-up reads low once the key is on. Two 3 mm magnets in the board pull it down onto the pins and line it up.

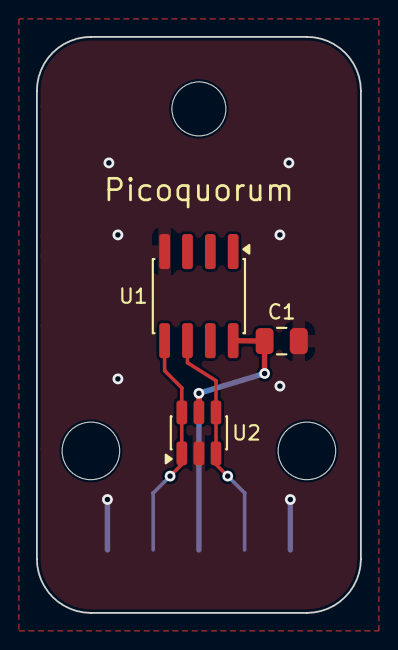
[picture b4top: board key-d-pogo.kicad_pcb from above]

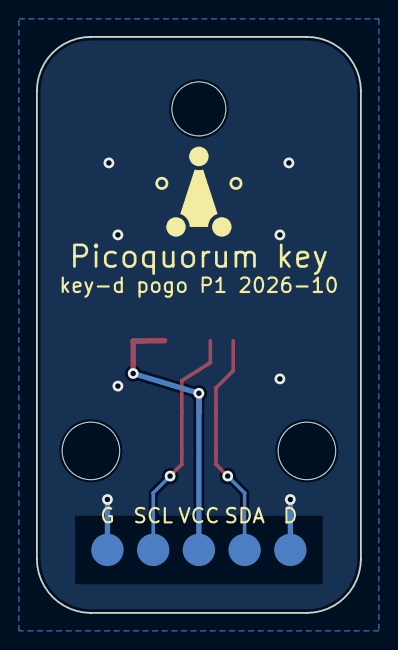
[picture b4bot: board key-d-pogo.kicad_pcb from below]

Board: 2 copper layers, 18.0 x 32.0 mm, 8 parts (2 on the bottom side), 4 nets.

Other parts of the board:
H1: Lanyard; MountingHole_3mm
H2, H3: Magnet; MountingHole_3.2mm_M3
LOGO1: PicoQuorum_Mark

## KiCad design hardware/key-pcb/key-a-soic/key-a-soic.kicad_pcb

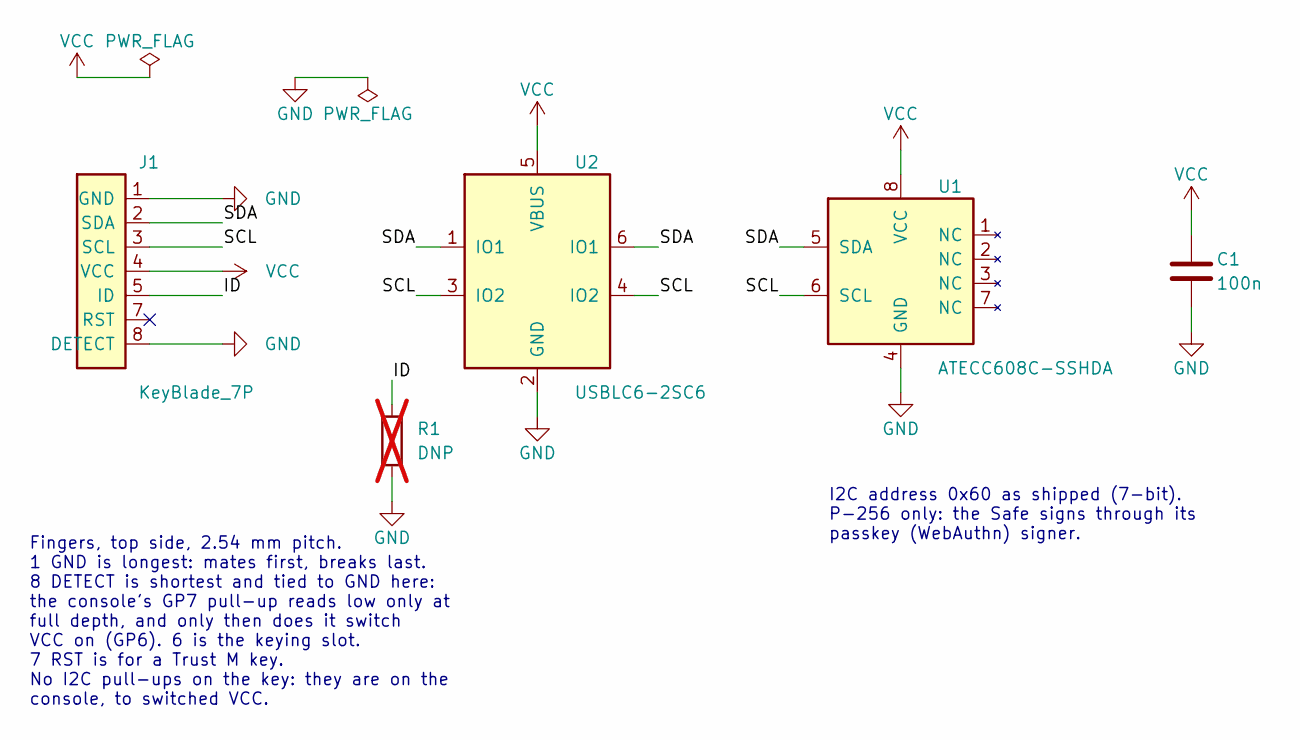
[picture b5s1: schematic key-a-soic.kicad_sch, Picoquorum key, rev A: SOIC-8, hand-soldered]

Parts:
C1: 100n; C_0805_2012Metric; LCSC C49678
J1: KeyBlade_7P; KeyBlade_7P_P2.54mm
R1: DNP; R_0805_2012Metric; not fitted
U1: ATECC608C-SSHDA; SOIC-8_3.9x4.9mm_P1.27mm; MPN ATECC608C-SSHDA-B; LCSC C28975195
U2: USBLC6-2SC6; SOT-23-6; MPN USBLC6-2SC6; LCSC C7519

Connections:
/ID: J1.5 (ID), R1.1
/SCL: J1.3 (SCL), U1.6 (SCL), U2.3 (IO2), U2.4 (IO2)
/SDA: J1.2 (SDA), U1.5 (SDA), U2.1 (IO1), U2.6 (IO1)
GND: C1.2, J1.1 (GND), J1.8 (DETECT), R1.2, U1.4 (GND), U2.2 (GND)
VCC: C1.1, J1.4 (VCC), U1.8 (VCC), U2.5 (VBUS)

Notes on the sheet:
Fingers, top side, 2.54 mm pitch. 1 GND is longest: mates first, breaks last. 8 DETECT is shortest and tied to GND here: the console's GP7 pull-up reads low only at full depth, and only then does it switch VCC on (GP6). 6 is the keying slot. 7 RST is for a Trust M key. No I2C pull-ups on the key: t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
I2C address 0x60 as shipped (7-bit). P-256 only: the Safe signs through its passkey (WebAuthn) signer.

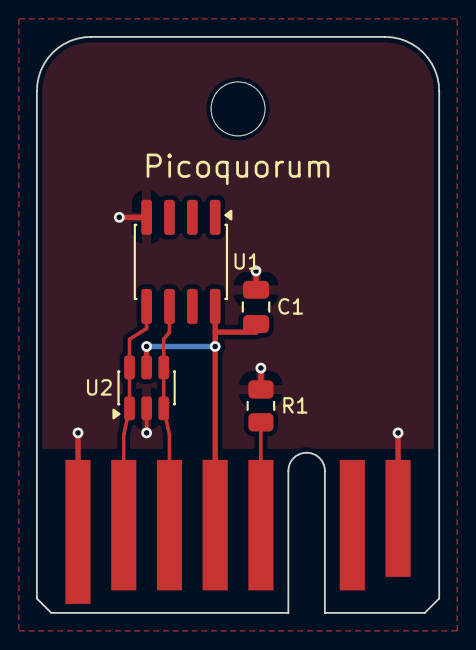
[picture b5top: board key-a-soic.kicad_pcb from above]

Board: 2 copper layers, 22.3 x 32.0 mm, 6 parts (0 on the bottom side), 5 nets.

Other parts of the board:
H1: Lanyard; MountingHole_3mm
